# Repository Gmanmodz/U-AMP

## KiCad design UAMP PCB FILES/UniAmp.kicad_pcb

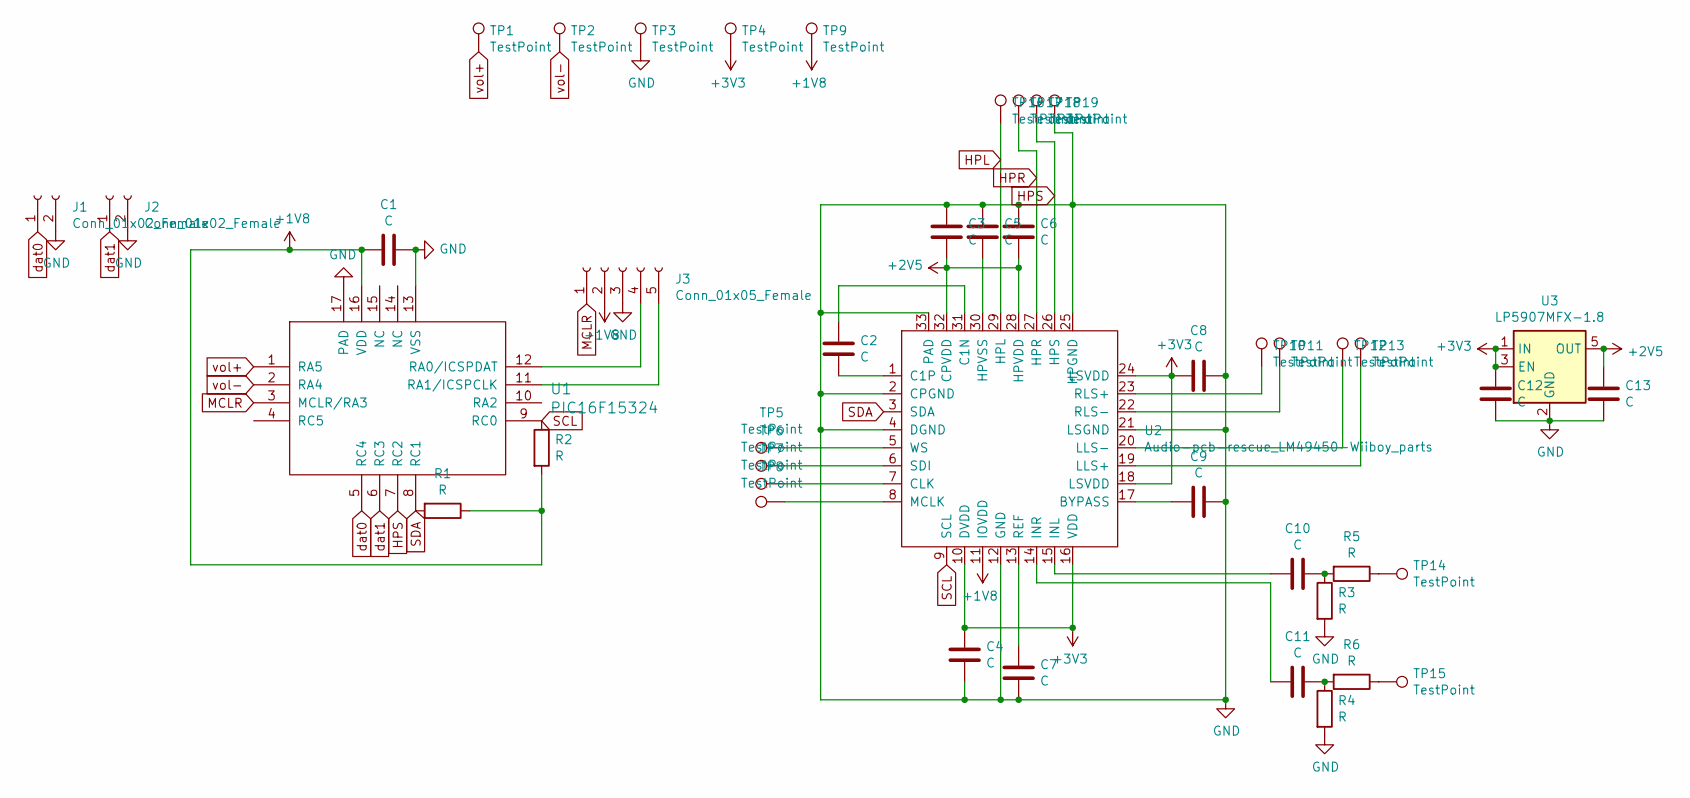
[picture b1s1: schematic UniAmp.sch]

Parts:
C1, C2, C3, C4, C5, C6, C7, C8, C9, C10, C11, C12, C13: C; C_0603_1608Metric
J1, J2: Conn_01x02_Female; SolderJumper-2_P1.3mm_Open_RoundedPad1.0x1.5mm
J3: Conn_01x05_Female; PinHeader_1x05_P1.27mm_Vertical
R1, R2, R3, R4, R5, R6: R; R_0603_1608Metric
TP1, TP2, TP3, TP4, TP5, TP6, TP7, TP8, TP9, TP10, TP11, TP12, TP13, TP14, TP15, TP16, TP17, TP18, TP19: TestPoint; 1.25mm pad
U1: PIC16F15324; QFN-16-1EP_4x4mm_P0.65mm_EP2.7x2.7mm
U2: Audio-pcb-rescue_LM49450-Wiiboy_parts; QFN-32-1EP_5x5mm_P0.5mm_EP3.1x3.1mm
U3: LP5907MFX-1.8; SOT-23-5

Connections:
+1V8: C1.2, J3.2, R1.1, R2.2, TP9.1, U1.16 (VDD), U2.11 (IOVDD)
+2V5: C3.2, C6.2, C13.1, U2.28 (HPVDD), U2.32 (CPVDD), U3.5 (OUT)
+3V3: C4.1, C8.2, C12.1, TP4.1, U2.10 (DVDD), U2.16 (VDD), U2.18 (LSVDD), U2.24 (LSVDD), U3.1 (IN), U3.3 (EN)
GND: C1.1, C3.1, C4.2, C5.1, C6.1, C7.2, C8.1, C9.1, C12.2, C13.2, J1.2, J2.2, J3.3, R3.2, R4.2, TP3.1, TP19.1, U1.13 (VSS), U1.17 (PAD), U2.2 (CPGND), U2.4 (DGND), U2.12 (GND), U2.21 (LSGND), U2.25 (HPGND), U2.33 (PAD), U3.2 (GND)
HPL: TP16.1, U2.29 (HPL)
HPR: TP17.1, U2.27 (HPR)
HPS: TP18.1, U1.7 (RC2), U2.26 (HPS)
MCLR: J3.1, U1.3 (MCLR/RA3)
unnamed: C2.1, U2.31 (C1N)
unnamed: C2.2, U2.1 (C1P)
unnamed: C5.2, U2.30 (HPVSS)
unnamed: C7.1, U2.13 (REF)
unnamed: C9.2, U2.17 (BYPASS)
unnamed: C10.1, R3.1, R5.2
unnamed: C10.2, U2.15 (INL)
unnamed: C11.1, R4.1, R6.2
unnamed: C11.2, U2.14 (INR)
unnamed: J3.4, U1.12 (RA0/ICSPDAT)
unnamed: J3.5, U1.11 (RA1/ICSPCLK)
unnamed: R5.1, TP14.1
unnamed: R6.1, TP15.1
unnamed: TP5.1, U2.5 (WS)
unnamed: TP6.1, U2.6 (SDI)
unnamed: TP7.1, U2.7 (CLK)
unnamed: TP8.1, U2.8 (MCLK)
unnamed: TP10.1, U2.23 (RLS+)
unnamed: TP11.1, U2.22 (RLS-)
unnamed: TP12.1, U2.20 (LLS-)
unnamed: TP13.1, U2.19 (LLS+)
SCL: R2.1, U1.9 (RC0), U2.9 (SCL)
SDA: R1.2, U1.8 (RC1), U2.3 (SDA)
dat0: J1.1, U1.5 (RC4)
dat1: J2.1, U1.6 (RC3)
vol+: TP1.1, U1.1 (RA5)
vol-: TP2.1, U1.2 (RA4)

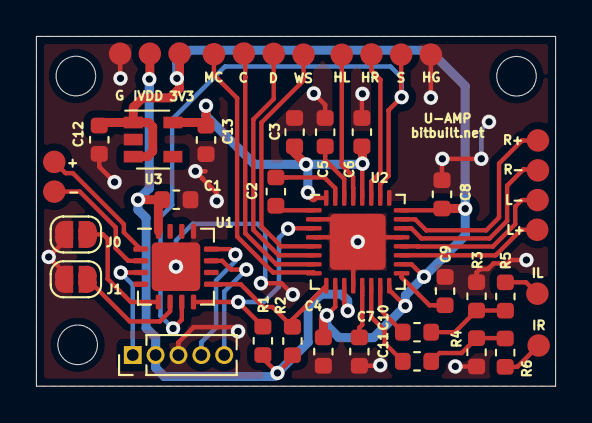
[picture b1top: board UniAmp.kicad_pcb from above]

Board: 2 copper layers, 28.8 x 19.4 mm, 44 parts (0 on the bottom side), 35 nets.

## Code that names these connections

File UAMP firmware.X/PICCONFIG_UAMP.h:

/* 
 * File:   PICCONFIG.c
 * Author: Gunnar T
 * Comments:
 * Revision history: 
 */
 
#ifndef PICCONFIG_UAMP_H
#define	PICCONFIG_UAMP_H

// PIC16F15324 Configuration Bit Settings

#define _XTAL_FREQ 32000000
#define TMR1_RST    65228

// CONFIG1
#pragma config FEXTOSC = OFF    // External Oscillator mode selection bits (Oscillator not enabled)
#pragma config RSTOSC = HFINT32 // Power-up default value for COSC bits (HFINTOSC with OSCFRQ= 32 MHz and CDIV = 1:1)
#pragma config CLKOUTEN = OFF   // Clock Out Enable bit (CLKOUT function is disabled; i/o or oscillator function on OSC2)
#pragma config CSWEN = ON       // Clock Switch Enable bit (Writing to NOSC and NDIV is allowed)
#pragma config FCMEN = ON       // Fail-Safe Clock Monitor Enable bit (FSCM timer enabled)

// CONFIG2
#pragma config MCLRE = OFF      // Master Clear Enable bit (MCLR pin function is port defined function)
#pragma config PWRTE = OFF      // Power-up Timer Enable bit (PWRT disabled)
#pragma config LPBOREN = OFF    // Low-Power BOR enable bit (ULPBOR disabled)
#pragma config BOREN = OFF      // Brown-out reset enable bits (Brown-out Reset Enabled, SBOREN bit is ignored)
#pragma config BORV = LO        // Brown-out Reset Voltage Selection (Brown-out Reset Voltage (VBOR) set to 1.9V on LF, and 2.45V on F Devices)
#pragma config ZCD = OFF        // Zero-cross detect disable (Zero-cross detect circuit is disabled at POR.)
#pragma config PPS1WAY = OFF    // Peripheral Pin Select one-way control (The PPSLOCK bit can be set and cleared repeatedly by software)
#pragma config STVREN = ON      // Stack Overflow/Underflow Reset Enable bit (Stack Overflow or Underflow will cause a reset)

// CONFIG3
#pragma config WDTCPS = WDTCPS_13// WDT Period Select bits (Divider ratio 1:262144)
#pragma config WDTE = OFF        // WDT operating mode (WDT enabled regardless of sleep; SWDTEN ignored)
#pragma config WDTCWS = WDTCWS_7// WDT Window Select bits (window always open (100%); software control; keyed access not required)
//#pragma config WDTCCS = HFINTOSC// WDT input clock selector (WDT reference clock is the 31.25 kHz HFINTOSC)
#pragma config WDTCCS = LFINTOSC// WDT input clock selector (WDT reference clock is the 31.0kHz LFINTOSC output)

// CONFIG4
#pragma config BBSIZE = BB512   // Boot Block Size Selection bits (512 words boot block size)
#pragma config BBEN = OFF       // Boot Block Enable bit (Boot Block disabled)
#pragma config SAFEN = OFF      // SAF Enable bit (SAF disabled)
#pragma config WRTAPP = OFF     // Application Block Write Protection bit (Application Block not write protected)
#pragma config WRTB = OFF       // Boot Block Write Protection bit (Boot Block not write protected)
#pragma config WRTC = OFF       // Configuration Register Write Protection bit (Configuration Register not write protected)
#pragma config WRTSAF = OFF     // Storage Area Flash Write Protection bit (SAF not write protected)
#pragma config LVP = OFF         // Low Voltage Programming Enable bit (Low Voltage programming enabled. MCLR/Vpp pin function is MCLR.)

// CONFIG5
#pragma config CP = OFF         // UserNVM Program memory code protection bit (UserNVM code protection disabled)

//Pin definitions
#define vol_plus    RA5
#define vol_minus   RA4
#define dat0        RC4
#define dat1        RC3
#define HPS         RC2

#include <xc.h> // include processor files - each processor file is guarded.  

#endif	

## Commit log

2019-11-09 Added firmware files
2019-11-10 mute
    added logic for handling mute when both buttons are pressed.
2019-11-10 added logic for seperate HP and SP volumes
2020-01-01 Changed to LF pic and turned off brownout reset
2020-01-02 Added pcb files
2020-01-02 Added BOM
2020-01-08 added 50ms delay at beginning of code
2020-04-18 Changed the PS2 I2S config
    Found a mistake in the config that caused distortion on audio peaks.
